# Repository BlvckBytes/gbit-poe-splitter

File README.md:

# gbit-poe-splitter

Power devices which don't support PoE and fine-adjust the received voltage at the same time. This equipment conforms to the *802.3at* standard, also known as *PoE+*.

⚠️ Use at your own risk and always properly test the product before connecting expensive gear up to it!

## Table of Contents

* [Goals](#goals)
* [The Product](#the-product)
* [Introduction](#introduction)
  * [802\.3af (PoE)](#8023af-poe)
  * [802\.3at (PoE\+)](#8023at-poe)
  * [802\.3bt (Hi\-PoE, PoE\+\+)](#8023bt-hi-poe-poe)
* [Concept](#concept)
* [Features](#features)
  * [Ports](#ports)
  * [Settings](#settings)
  * [Status LEDs](#status-leds)
* [Parts](#parts)
* [Prototyping](#prototyping)
  * [Summary](#summary)

## Goals

* ✅ Small footprint PCB
* ✅ Max budget of 15 Euros
* ✅ Support up to 60V of input
* ✅ Selectable output voltage
* ✅ Selectable PoE class
* ✅ Highest possible current throughput
* ✅ Indication of active type 2
* ✅ DC Output Jack
* ✅ Proper centertap-termination

## The Product

## Introduction

PoE is short for *Power over Ethernet* and will allow to transmit the needed power for devices on the other end of the CAT-X cable. This is especially of interest for already existing infrastructure, where it's just not economical to run a separate power wire. The only drawbacks are that there's a limit to how much energy can be transmitted and that you might experience a voltage-drop and thus an energy-loss over longer distances of wire.

### 802.3af (PoE)

This standard adds power-delivery to *802.3*, with up to *15.4W* at the output of the power sourcing equipment (PSE), using two twisted-pairs for injection. After calculating the average real world losses over the wire , the consumer only receives around *12.95W* of power. There are also lower power-classes, which are not the default and need to be registered for by the powered device (PD) explicitely.

| Class | Min Power (at PD, [W]) | Max Power (at PD, [W]) |
|:------|:----------|:----------|
| 0 | 0.44 | 12.95 |
| 1 | 0.44 | 3.84 |
| 2 | 3.84 | 6.49 |
| 3 | 6.49 | 12.95 |

### 802.3at (PoE+)

Since *802.3af* is not sufficient for some standard usecases, *802.3at* bumps it up a notch, while still using only two twisted-pairs. Now, PDs can receive up to *25.5W*, which should be plenty for switches, access-points, VOIP, card-readers and so on and so forth.

| Class | Min Power (at PD, [W]) | Max Power (at PD, [W]) |
|:------|:----------|:----------|
| 4 | 12.95 | 25.5 |

### 802.3bt (Hi-PoE, PoE++)

In order to meet the higher demand of power in special cases, IEEE came up with this standard at the end of 2018. Instead of two pairs, it uses all four pairs for power delivery, which will allow up to **100 watts**. Power loss gets cut in half, at least in theory. Since this standard requires more expensive technology, it's not covered by this project.

## Concept

There are several [requirements](https://www.ieee802.org/3/poep_study//email/pdf00005.pdf) to the PD, if it wants to consume *802.3at*.

The main component is represented by the [H6062NL](https://eu.mouser.com/ProductDetail/Pulse-Electronics/H6062NL?qs=hlTQ6wBu%252Bnnq8WII%2F92SGQ%3D%3D), which is a signal transformer that supports up to *1000Base-T*. It consits of four individual isolation transformers, which offer a center-tap for power delivery purposes, where one transformer corresponds to one twisted pair, to fully isolate the PD.

In order to support detection, classification, inrush-current limiting and short-circuit protection, I decided on the [TPS2379](https://www.ti.com/lit/ds/symlink/tps2379.pdf?ts=1636211997743&ref_url=https%253A%252F%252Fwww.google.com%252F). It supports up to *1A* of operating current, which should be plenty, and can even be extended using an external mosfet.

To tap the available power from either one of the two pairs, and to handle reverse-polarity situations, two full bridge rectifiers are inserted directly inbetween the transformers and the control-IC. The output voltage will then be fed through a buck-converter, to easily regulate it. [LM2596HV](http://hmsemi.com/downfile/LM2596HV.PDF) seems to be a perfect fit for this job.

### Detection

The PSE constantly pulses a 4-point detection signal on the port in question, which starts out `LOW` and then rises `HIGH` two times. With the known voltage potential, and the measurable current draw, the PSE calculates the inner resistance of the connected PD. It has to `23.75kOhm < R < 26.25kOhm`, to be a valid PoE device.

### Classification

After passing detection, the PD has to specify it's desired power class to the PSE. The PSE sends signals between 14.5V and 20.5V, while the PD removes R_DET from the line and applies R_CLS, in series with a constant 2.5V regulator. This way, the PSE can accurately measure the current flowing through R_CLS, and thus determine the desired class.

After completing both steps successfully, power is activated.

## Features

### Ports

* Ethernet in (from PSE)
* Ethernet out (to non-PD)
* Standard DC-jack to supply power

### Settings

* 5 positions for class 0-4
* Voltage regulation potentiometer

### Status LEDs

* Power available (Yellow)
* Inrush current limiting (Yellow)
* Type 2 active (Yellow)
* Pair 1 & 2 hot (Red)
* Pair 3 & 4 hot (Red)

## Parts

| Part | Description | Shop | Price/Pice | Amount | Total |
|:-----|:------------|:-----|:-----------|:-------|:------|
| **Integrated Circuits** |
| H6062NL | Signal Transformer | Mouser | 4.27€ | 1 | 4.27€ |
| TPS2379 | 802.3af PD Interface | Mouser | 2.35€ | 1 | 2.35€ |
| MB1S-TP | Bridge Rectifier | Mouser | 0.26€ | 2 | 0.52€ |
| LM2596HV | [Regulator & aux. Components](https://de.aliexpress.com/item/32916300929.html?spm=a2g0s.9042311.0.0.55414c4dqviJXF) | AliExpress | 1.12€ | 1 | 1.12€ |
| SI7454FDP-T1-RE3 | N-Channel Mosfet | Mouser | 0.69€ | 1 | 0.69€ |
| **Connectors** |
| RJLSE4118101 | RJ45 8P8C Shielded | Mouser | 0.91€ | 2 | 1.82€ |
| PRT-10811 | 5.5mm DC Jack | Mouser | 0.81€ | 1 | 0.81€ |
| **Status LEDs** |
| CRCW060310K0FKTC | 10k Ohm 0603 | Mouser | 0.022€ | 5 | 0.11€ |
| 150060GS75000 | LED Yellow 0603 | Mouser | 0.12€ | 3 | 0.24€ |
| 150060GS75000 | LED Red 0603 | Mouser | 0.12€ | 2 | 0.24€ |
| **Filtering & Termination** |
| RC0603FR-0775RL | 75 Ohm 0603 | Mouser | 0.006€ | 8 | 0.012€ |
| CL10B103KO8NNNC | 10nF 0603 | Mouser | 0.011€ | 4 | 0.044€ |
| C0805C104K8RACAUTO | 100nF 0805 | Mouser | 0.058€ | 1 | 0.058€ |
| CL10C102JB8NNND | 1nF 0603 | Mouser | 0.016€ | 2 | 0.032€ |
| **PoE Class (R_CLS)** |
| RC0603FR-071K27L | 1.27k Ohm 0603 | Mouser | 0.008€ | 1 | 0.008€ |
| CR0603-FX-2430ELF | 243 Ohm 0603 | Mouser | 0.016€ | 1 | 0.016€ |
| ERJ-3EKF1370V | 137 Ohm 0603 | Mouser | 0.014€ | 2 | 0.014€ |
| CR0603-FX-90R9ELF | 90.9 Ohm 0603 | Mouser | 0.013€ | 1 | 0.013€ |
| CR0603-FX-63R4ELF | 63.4 Ohm 0603 | Mouser | 0.013€ | 1 | 0.013€ |
| **R_DEN** |
| RK73H1JTTDD2492F | 24.9k Ohm 0603 | Mouser | 0.01€ | 1 | 0.01€ |
| **Miscellaneous** |
| RK73B1JTTD204J | 200k Ohm 0603 | Mouser | 0.008€ | 1 | 0.008€ |
| GS2M-LTP | Rectifier Diode | Mouser | 0.28€ | 2 | 0.56€ |
| ACP 6-SMD 10K | SMD Trimmer | Reichelt AT | 0.30€ | 1 | 0.30€ |

Total: ~13€

## Prototyping

07.11.2021:

I wanted to check if I could extract power using only the transformer, like some people managed to do online, with no additional logic. After finding an old gigabit-capable router in my basement, I disassembled it and unsoldered one of it's internal transformators ([G4802CG](https://media.digikey.com/pdf/Data%20Sheets/Mentech%20PDFs/G4802CG.pdf)). I also tried one from a 100M model, which didn't work, because they've joined up the centertaps on neighboring coils. The pins were so small that a breakout-board was necessary. This was my test-setup:

On the left, the PSE is connected, where the power gets extracted, and on the right, it's my laptop (PD). I'm using a `Netgear GS305P`, and nope, it's not directly spitting out power without additional logic. I actually discovered that it pulses a few volts on all ports, no matter if something is connected or not. I guess that's where the PD would use load modulation to register itself and it's desired power-class. Now I'm waiting to receive my mouser-order to continue with this test-setup, until the first prototype is up and working, only then will I create a full PCB-layout.

Just in case you're wondering, here's whats inside the IC, I think it looks wonderful:

09.11.2021:

Yesterday and today I finally created all missing footprints and symbols to create the first revision of the schematic. I tried to keep it organized through grouping by functional blocks, as you usually do. Still need to revise it, before I go into routing the board.

Now that the schematic is done, I started on some small parts of routing. I kinda want to have the ethernet ports on one side of the board next to each other, and the DC jack vis-a-vis. The ethernet signal lines are basically just passed through the transformer, which should be done in a short and "bus-like" fashion.

10.11.2021:

The board is completely routed out now, all airwires have been connected. Looks quite nice so far, I don't think that I can squeeze it any tighter without going down yet another rabbit-hole.

After correcting other small mistakes, the first physical prototype has been created.

First, I created a double-sided "pouch" out of two overhead projector sheets, having the printed (toner) sides facing together. To block out most tiny holes, I overlayed two sheets of each side. My trusty `HP LaserJet 1200` did a great job again.

After exposing, I developed the foto-resist and then etched away unmasked sections using [sodium persulfate](https://solectroshop.com/en/grabado-de-circuito/455-1kg-de-persulfato-de-sodio-pcb-etchant-para-circuitos-impresos.html), while I heated the solution using the exhaust of my computer, ;).

Quite pleased with the result, although I still need to continuity-check it using my multimeter.

Thankfully I managed to only need through-holes for 6 vias and the DC jack. I hate drilling, it's extremely hard to pull off accurately on such a scale. The holes on both sides lined up perfectly tho, I'm extremely happy about that.

The rivets also worked out okay-ish this time, since I'm going easier on them with the tool. It's still far from perfect, but I think it gets the job done.

13.11.2021:

After soldering all top-layer components, I tested the board for gbit-ethernet passthrough and low power pulse extraction (as it currently is without the controller IC), and everything works as expected.

### Summary

There have been many things I learned from the first prototype, as this project definitely has it's stumbling blocks...

1. The pair-indicator LEDs cannot be directly connected, as they change the resistive reading of the PSE, which therefore cannot act properly. Instead of wiring them to ground, I need to connect them to the PoE-IC's return pin.
2. Same issue as with the LEDs occurrs with the input smoothing cap. Also needs ground as return.
3. The external mosfet's package is extremely cumbersome for DIY, change that.
4. LEDs need a higher resistance, as 1.9kOhm just doesn't cut it. They almost burn at 40+V.

Everything else seems to be okay so far, just that with a small load of - for example - 1kOhm, the PSE disconnects power when the current-draw drops below around 10mA. Would be great if there was a fallback load, so that power regulation is possible down to a few volts.

16.11.2021:

After taking a short break from this project, I now fixed the issues within my layout and managed to squeeze things even tighter, shaving off a few more millimeters of length. The voltage regulation also seems to work perfectly without a load, the previous potentiometer was melted from all the hot air I used on the board, and the input smoothing cap probably also added some further power detection possibilities for the PSE. All up and running now.

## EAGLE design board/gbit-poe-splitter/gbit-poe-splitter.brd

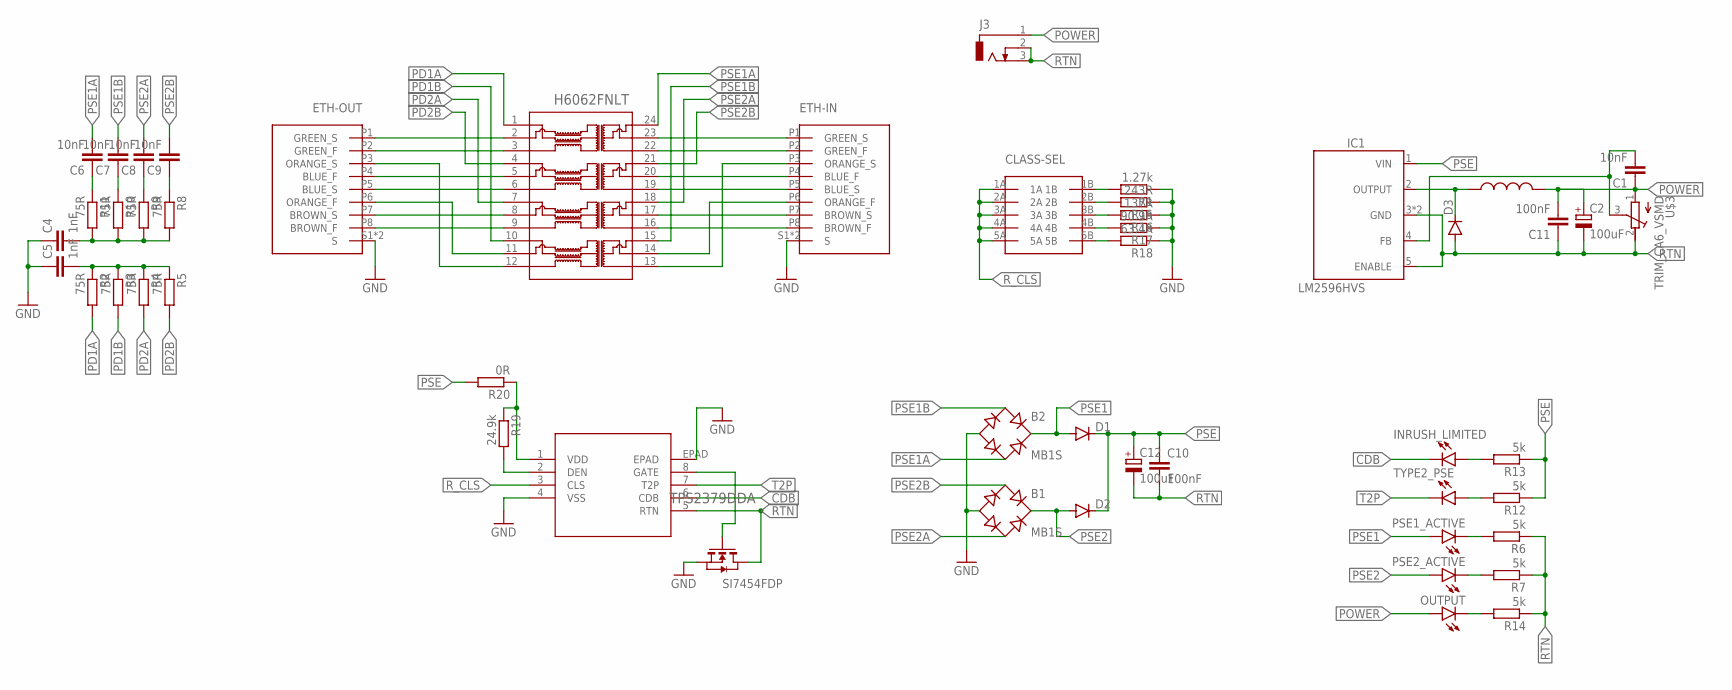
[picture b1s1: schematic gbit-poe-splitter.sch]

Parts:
B1, B2: MB1S; SOIC-4
C1, C6, C7, C8, C9: 10nF; C0603K
C2, C12: 100uF; 153CLV-1012
C4, C5: 1nF; C0603K
C10, C11: 100nF; C0805
CLASS-SEL: 54202-T0803AB01LF
D1, D2, D3: DIODE-DO-214AC; DO-214AC
ETH-IN: RJLSE-4X1XX-01
ETH-OUT: RJLSE-4X1XX-01
IC1: LM2596HVS; TO263-5
INRUSH_LIMITED: LEDCHIPLED_0603; CHIPLED_0603
J3: DCJ0303
OUTPUT: LEDCHIPLED_0603; CHIPLED_0603
PSE1_ACTIVE, PSE2_ACTIVE: LEDCHIPLED_0603; CHIPLED_0603
R1: 1.27k; R0603
R2, R3, R4, R5, R8, R9, R10, R11: 75R; R0603
R6, R7, R12, R13, R14: 5k; R0603
R15: 243R; R0603
R16: 137R; R0603
R17: 90.9R; R0603
R18: 63.4R; R0603
R19: 24.9k; R0603
R20: 0R; R1206
TYPE2_PSE: LEDCHIPLED_0603; CHIPLED_0603
U1: TPS2379DDA; DDA8_3P1X2P4_TEX
U$1: SI7454FDP; POWERPAK-SO-8
U$2: INDUCTOR-SMD7070; INDUCTOR-SMD
U$3: TRIM_CA6_VSMD
XMER1: H6062FNLT; H6062FNLT_PUL

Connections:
CDB: INRUSH_LIMITED.C, U1.6 (CDB)
GND: B1.-, B2.-, C4.1, C5.1, ETH-IN.S1 (S), ETH-IN.S2 (S), ETH-OUT.S1 (S), ETH-OUT.S2 (S), R1.1, R15.1, R16.1, R17.1, R18.1, U1.4 (VSS), U1.EPAD, U$1.S1 (S), U$1.S2 (S), U$1.S3 (S)
unnamed: ETH-OUT.P1 (GREEN_S), XMER1.2
unnamed: ETH-OUT.P2 (GREEN_F), XMER1.3
unnamed: ETH-OUT.P3 (ORANGE_S), XMER1.12
unnamed: ETH-OUT.P4 (BLUE_F), XMER1.5
unnamed: ETH-OUT.P5 (BLUE_S), XMER1.6
unnamed: ETH-OUT.P6 (ORANGE_F), XMER1.11
unnamed: ETH-OUT.P7 (BROWN_S), XMER1.8
unnamed: ETH-OUT.P8 (BROWN_F), XMER1.9
unnamed: ETH-IN.P7 (BROWN_S), XMER1.17
unnamed: ETH-IN.P4 (BLUE_F), XMER1.20
unnamed: ETH-IN.P8 (BROWN_F), XMER1.16
unnamed: ETH-IN.P5 (BLUE_S), XMER1.19
unnamed: ETH-IN.P6 (ORANGE_F), XMER1.14
unnamed: ETH-IN.P3 (ORANGE_S), XMER1.13
unnamed: ETH-IN.P2 (GREEN_F), XMER1.22
unnamed: ETH-IN.P1 (GREEN_S), XMER1.23
unnamed: C5.2, R2.1, R3.1, R4.1, R5.1
unnamed: C4.2, R8.2, R9.2, R10.2, R11.2
unnamed: C6.1, R11.1
unnamed: C7.1, R10.1
unnamed: C8.1, R9.1
unnamed: C9.1, R8.1
unnamed: PSE1_ACTIVE.C, R6.2
unnamed: PSE2_ACTIVE.C, R7.2
unnamed: R12.2, TYPE2_PSE.A
unnamed: INRUSH_LIMITED.A, R13.2
unnamed: OUTPUT.C, R14.2
unnamed: CLASS-SEL.1B, R1.2
unnamed: CLASS-SEL.2B, R15.2
unnamed: CLASS-SEL.3B, R16.2
unnamed: CLASS-SEL.4B, R17.2
unnamed: CLASS-SEL.5B, R18.2
unnamed: D3.C, IC1.2 (OUTPUT), U$2.1
unnamed: U1.8 (GATE), U$1.G
unnamed: R19.2, U1.2 (DEN)
unnamed: C1.2, IC1.4 (FB), U$3.3 (S)
unnamed: R19.1, R20.1, U1.1 (VDD)
PD1A: R2.2, XMER1.1
PD1B: R3.2, XMER1.10
PD2A: R4.2, XMER1.7
PD2B: R5.2, XMER1.4
POWER: C1.1, C2.+, C11.2, J3.1, OUTPUT.A, U$2.2, U$3.1 (A)
PSE: C10.1, C12.+, D1.C, D2.C, IC1.1 (VIN), R12.1, R13.1, R20.2
PSE1: B2.+, D1.A, PSE1_ACTIVE.A
PSE1A: B2.~2 (AC2), C6.2, XMER1.24
PSE1B: B2.~1 (AC1), C7.2, XMER1.15
PSE2: B1.+, D2.A, PSE2_ACTIVE.A
PSE2A: B1.~2 (AC2), C8.2, XMER1.18
PSE2B: B1.~1 (AC1), C9.2, XMER1.21
RTN: C2.-, C10.2, C11.1, C12.-, D3.A, IC1.3 (GND), IC1.5 (ENABLE), IC1.6 (GND), J3.2, J3.3, R6.1, R7.1, R14.1, U1.5 (RTN), U$1.D1 (D), U$1.D2 (D), U$1.D3 (D), U$1.D4 (D), U$1.DPAD (D), U$3.2 (E)
R_CLS: CLASS-SEL.1A, CLASS-SEL.2A, CLASS-SEL.3A, CLASS-SEL.4A, CLASS-SEL.5A, U1.3 (CLS)
T2P: TYPE2_PSE.C, U1.7 (T2P)

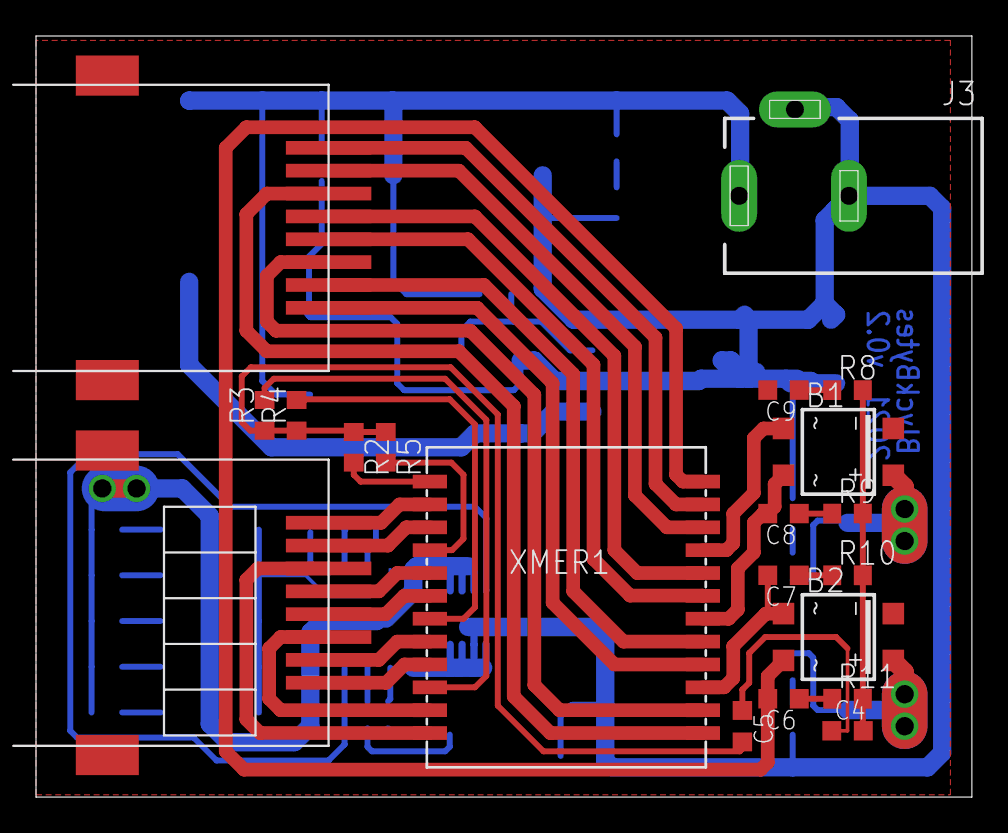
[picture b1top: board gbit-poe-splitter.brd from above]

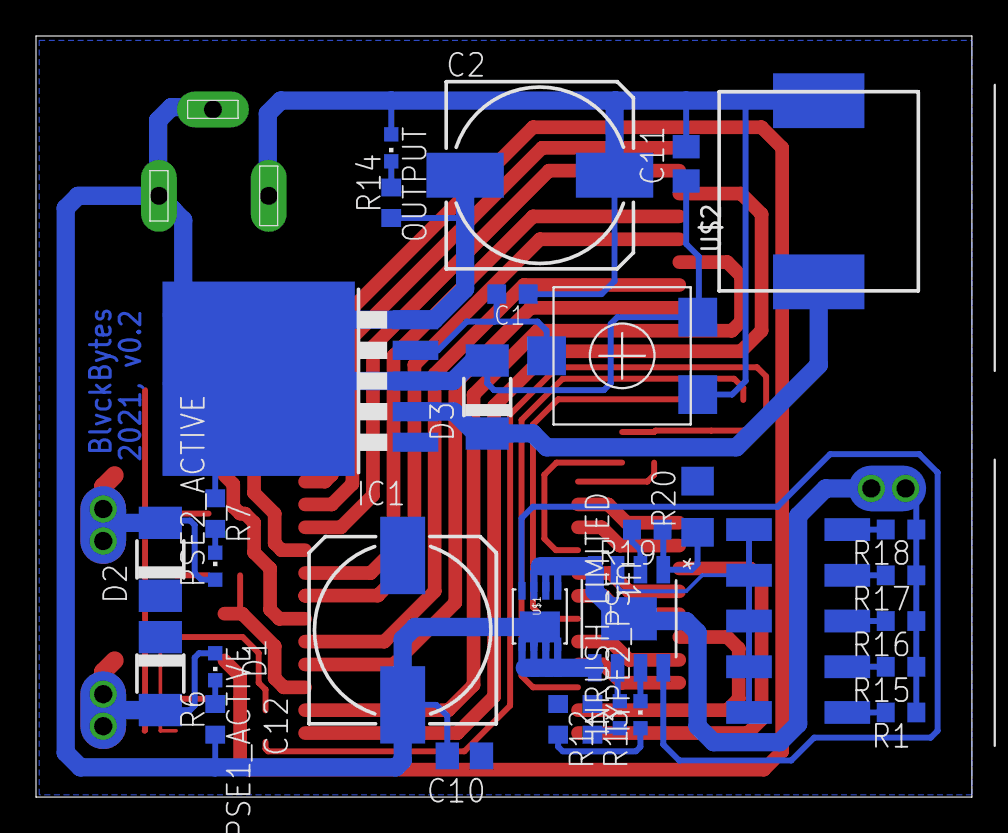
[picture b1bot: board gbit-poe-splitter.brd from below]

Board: 2 copper layers, 52.0 x 42.3 mm, 51 parts (31 on the bottom side), 54 nets.

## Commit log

2021-11-06 Chose a better RJ45-jack
2021-11-06 Added all parts, wrote features section, moved parts to EOF
2021-11-07 Wrote prototyping entry
2021-11-08 Documented DET and CLS processes
2021-11-08 Created and gathered custom libraries for parts, created base schematic file
2021-11-09 Created first revision of the full schematic
2021-11-09 Added part
2021-11-09 Began the routing process
2021-11-09 Routed top side of the board completely
2021-11-10 Completed board layout
2021-11-10 Fixed jack orientation, font and keepouts
2021-11-10 Documented first physical prototype
2021-11-10 Documented riveting
2021-11-10 Documented regulator testing
2021-11-12 Fixed horrible ethernet pin swap
2021-11-12 Updated schematic
2021-11-12 Added rivets documentation
2021-11-13 Added finished top image
2021-11-13 Wrote first prototype summary and added partial fixes to layout
2021-11-16 Fixed layout issues
2021-11-16 Fixed board edge
2021-11-17 Added finished product images

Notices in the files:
parts and their libraries:
COPYRIGHT: Copyright (C) 2021 Ultra Librarian. All rights reserved.
